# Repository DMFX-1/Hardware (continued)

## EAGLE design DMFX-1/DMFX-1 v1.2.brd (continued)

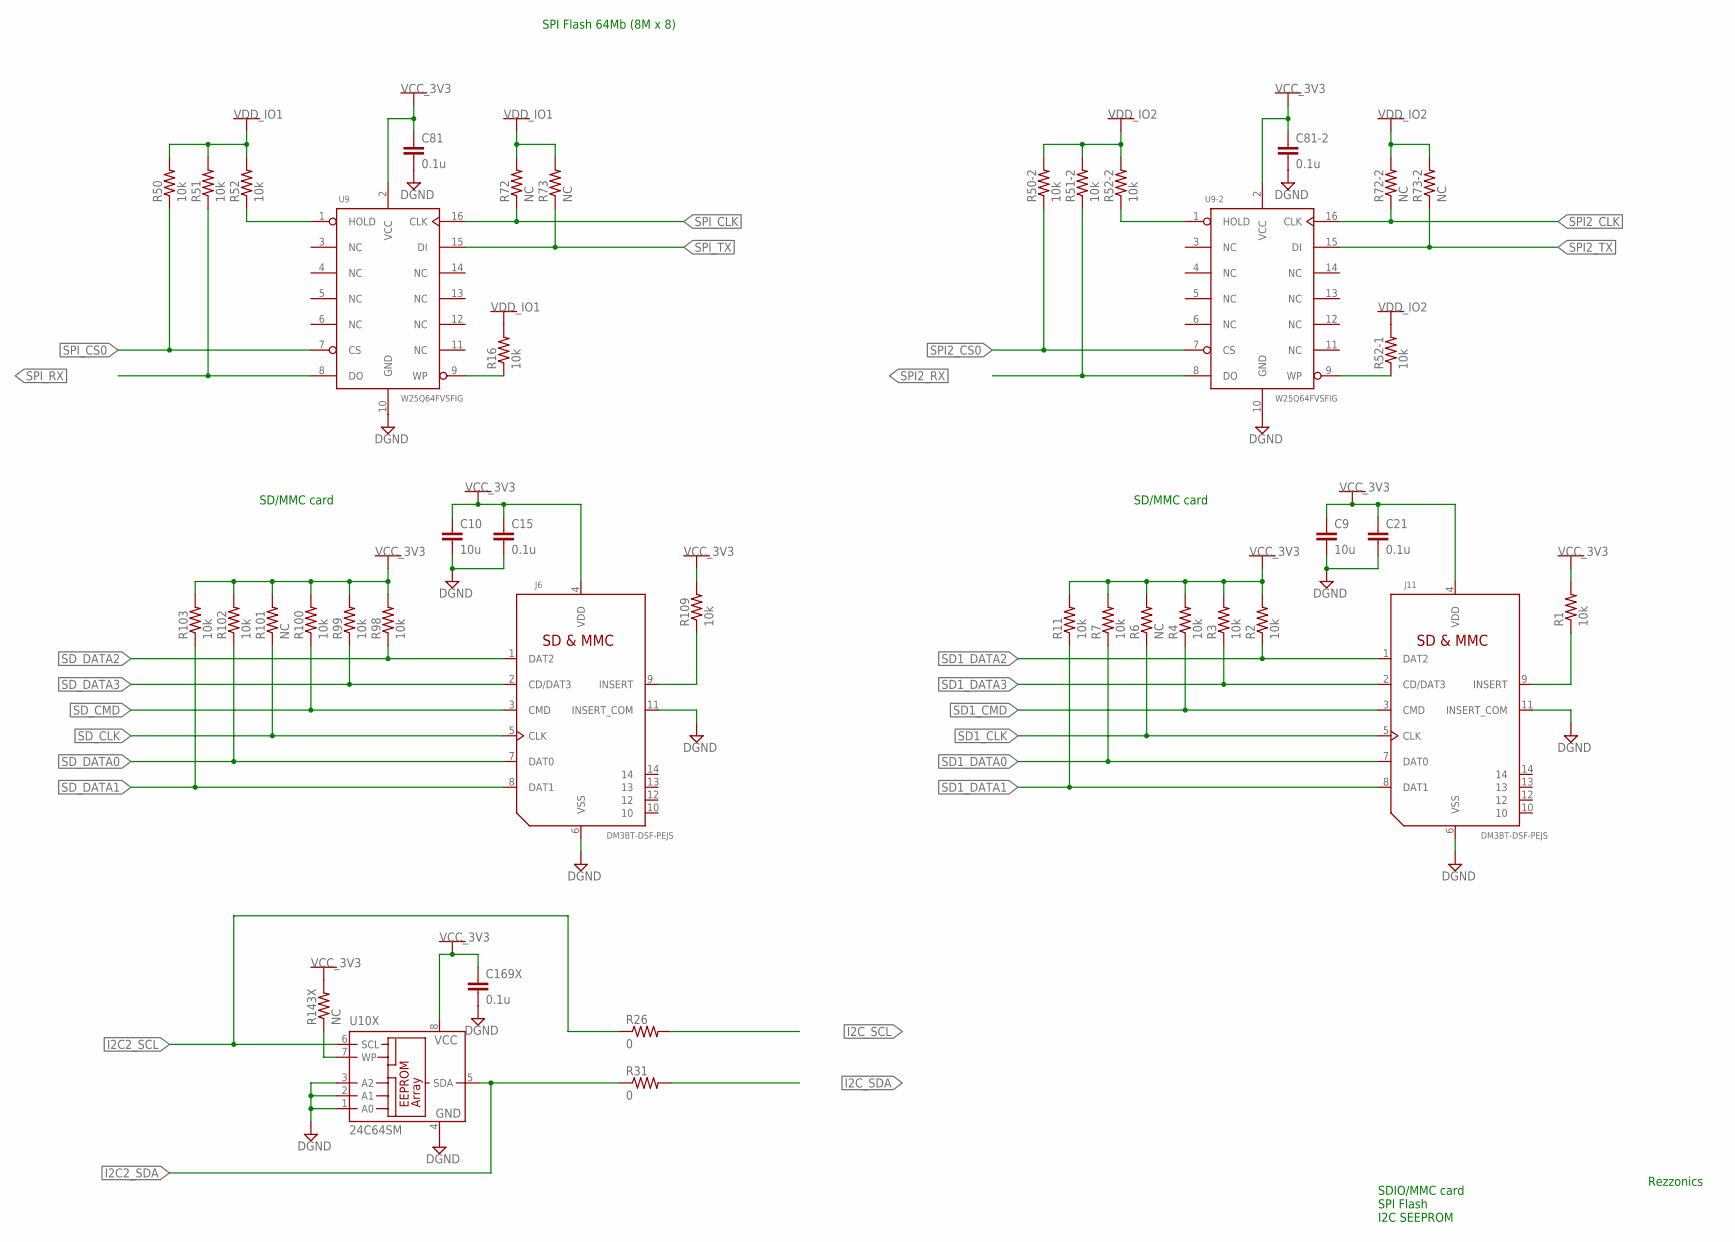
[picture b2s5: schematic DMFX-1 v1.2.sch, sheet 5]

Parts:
C9, C10: 10u; C0603K; MPN GRM188R61C106MA73D
C15, C21, C81, C81-2, C169X: 0.1u; C0402K; MPN GRM155R71C104JA88D
J6, J11: DM3BT-DSF-PEJS; MICROSD_RBT; MPN DM3BT-DSF-PEJS
R1, R2, R3, R4, R7, R11, R16, R50, R50-2, R51, R51-2, R52, R52-1, R52-2, R98, R99, R100, R102, R103, R109: 10k; 0402-RES; MPN ERJ-2RKF1002X
R6, R72, R72-2, R73, R73-2, R101: NC; 0402-RES; MPN *
R26, R31: 0; 0402-RES; MPN ERJ-2GE0R00X
R143X: NC; 0402-RES
U9, U9-2: W25Q64FVSFIG; SO16L; MPN W25Q64FVSFIG
U10X: 24C64SM; SO-08M; MPN AT24C64D-SSHM-T

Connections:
DGND: C9.2, C10.2, C15.2, C21.2, C81.2, C81-2.2, C169X.2, J6.6 (VSS), J6.11 (INSERT_COM), J11.6 (VSS), J11.11 (INSERT_COM), U9.10 (GND), U9-2.10 (GND), U10X.1 (A0), U10X.2 (A1), U10X.3 (A2), U10X.4 (GND); also elsewhere on the board
I2C2_SCL: R26.1, U10X.6 (SCL); also elsewhere on the board
I2C2_SDA: R31.1, U10X.5 (SDA); also elsewhere on the board
I2C_SCL: R26.2; also elsewhere on the board
I2C_SDA: R31.2; also elsewhere on the board
unnamed: J11.9 (INSERT), R1.1
unnamed: R16.1, U9.9 (WP)
unnamed: R52-1.1, U9-2.9 (WP)
unnamed: R52.1, U9.1 (HOLD)
unnamed: J6.9 (INSERT), R109.1
unnamed: R52-2.1, U9-2.1 (HOLD)
unnamed: R143X.1, U10X.7 (WP)
SD1_CLK: J11.5 (CLK), R6.1; also elsewhere on the board
SD1_CMD: J11.3 (CMD), R4.1; also elsewhere on the board
SD1_DATA0: J11.7 (DAT0), R7.1; also elsewhere on the board
SD1_DATA1: J11.8 (DAT1), R11.1; also elsewhere on the board
SD1_DATA2: J11.1 (DAT2), R2.1; also elsewhere on the board
SD1_DATA3: J11.2 (CD/DAT3), R3.1; also elsewhere on the board
SD_CLK: J6.5 (CLK), R101.1; also elsewhere on the board
SD_CMD: J6.3 (CMD), R100.1; also elsewhere on the board
SD_DATA0: J6.7 (DAT0), R102.1; also elsewhere on the board
SD_DATA1: J6.8 (DAT1), R103.1; also elsewhere on the board
SD_DATA2: J6.1 (DAT2), R98.1; also elsewhere on the board
SD_DATA3: J6.2 (CD/DAT3), R99.1; also elsewhere on the board
SPI2_CLK: R72-2.1, U9-2.16 (CLK); also elsewhere on the board
SPI2_CS0: R50-2.1, U9-2.7 (CS); also elsewhere on the board
SPI2_RX: R51-2.1, U9-2.8 (DO); also elsewhere on the board
SPI2_TX: R73-2.1, U9-2.15 (DI); also elsewhere on the board
SPI_CLK: R72.1, U9.16 (CLK); also elsewhere on the board
SPI_CS0: R50.1, U9.7 (CS); also elsewhere on the board
SPI_RX: R51.1, U9.8 (DO); also elsewhere on the board
SPI_TX: R73.1, U9.15 (DI); also elsewhere on the board
VCC_3V3: C9.1, C10.1, C15.1, C21.1, C81.1, C81-2.1, C169X.1, J6.4 (VDD), J11.4 (VDD), R1.2, R2.2, R3.2, R4.2, R6.2, R7.2, R11.2, R98.2, R99.2, R100.2, R101.2, R102.2, R103.2, R109.2, R143X.2, U9.2 (VCC), U9-2.2 (VCC), U10X.8 (VCC); also elsewhere on the board
VDD_IO1: R16.2, R50.2, R51.2, R52.2, R72.2, R73.2; also elsewhere on the board
VDD_IO2: R50-2.2, R51-2.2, R52-1.2, R52-2.2, R72-2.2, R73-2.2; also elsewhere on the board

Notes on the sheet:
SD/MMC card
SPI Flash 64Mb (8M x 8)
Rezzonics
SDIO/MMC card SPI Flash I2C SEEPROM

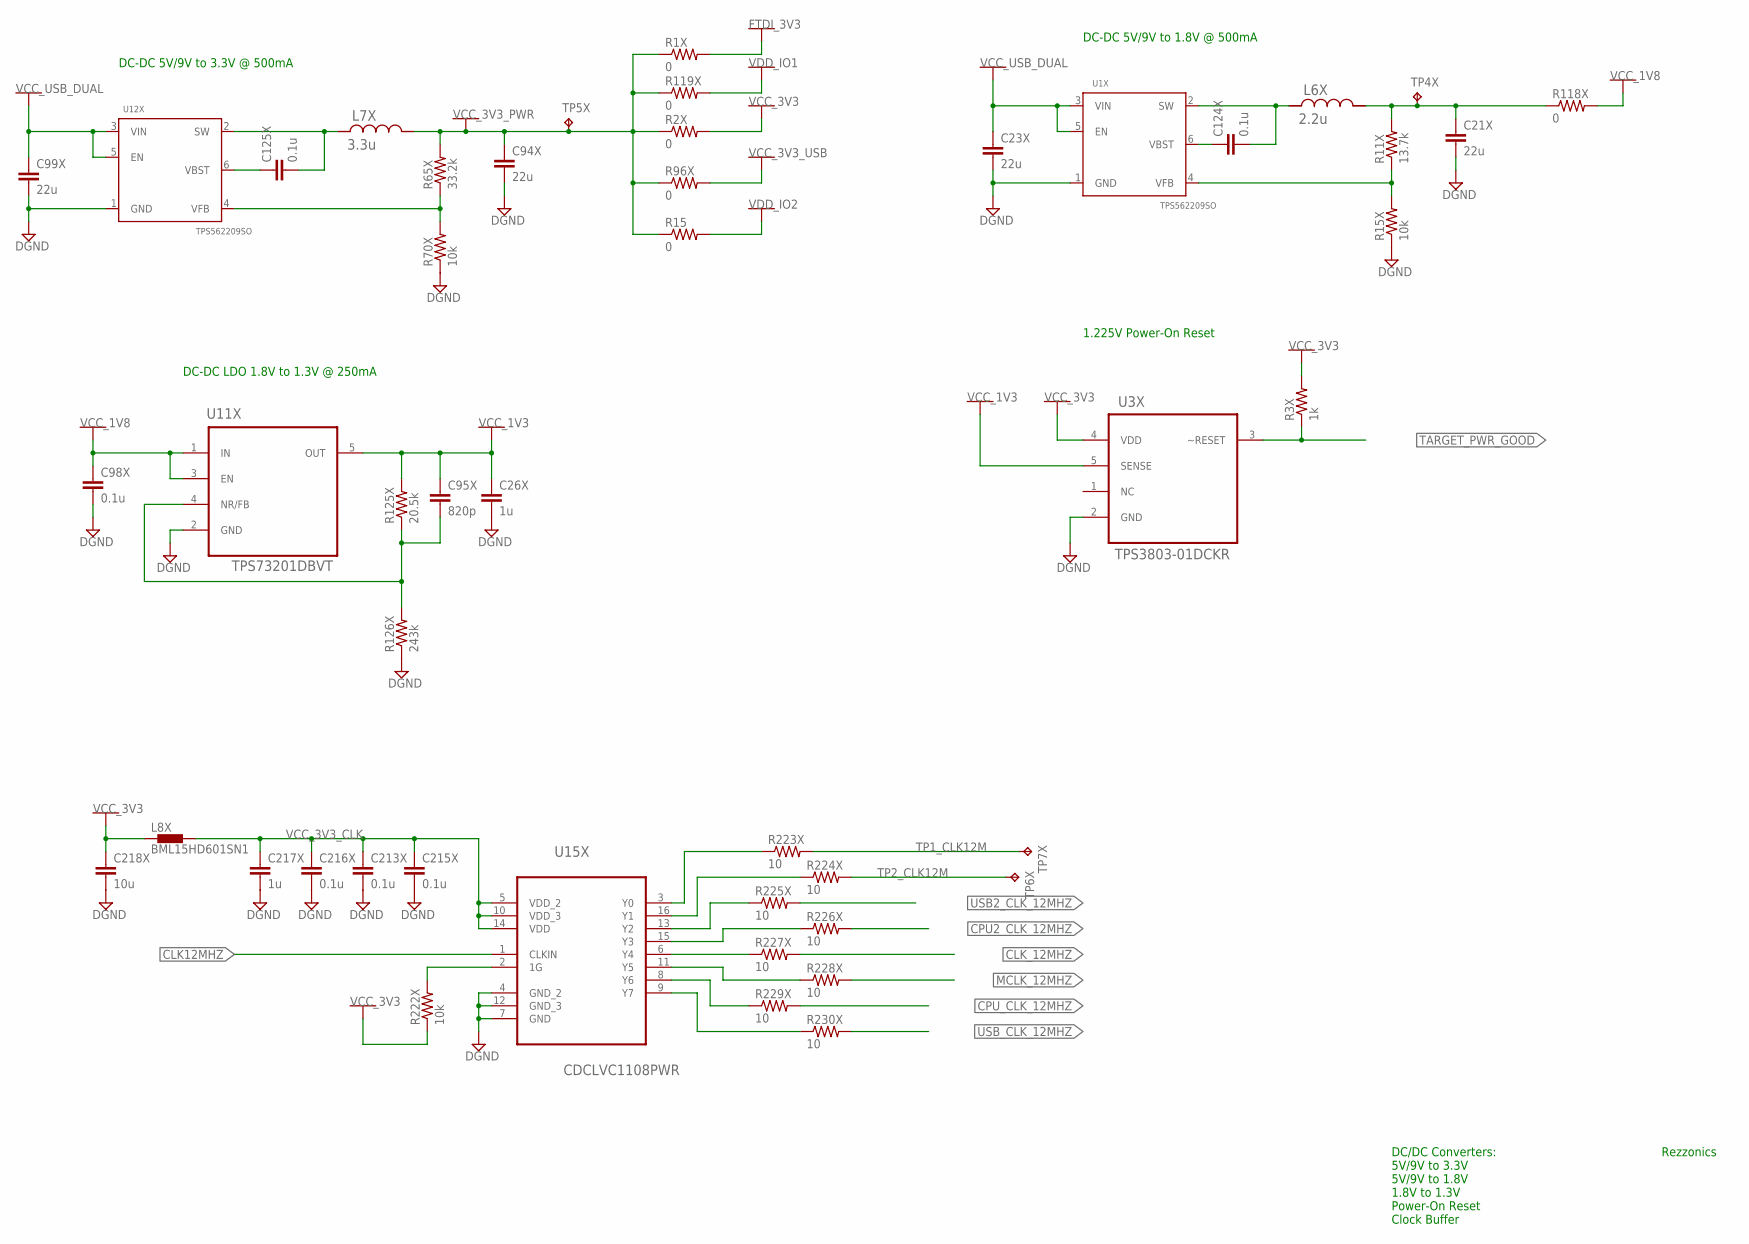
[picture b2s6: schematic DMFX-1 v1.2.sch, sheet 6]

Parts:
C21X, C94X: 22u; C1206K; MPN GRM31CR71A226KE15L
C23X, C99X: 22u; C1210K; MPN GRM32ER71E226ME15L
C26X, C217X: 1u; C0402K; MPN GRM155R70J105KA12D
C95X: 820p; C0402K; MPN GRM1555C1H821JA01D
C98X, C124X, C125X, C213X, C215X, C216X: 0.1u; C0402K; MPN GRM155R71C104JA88D
C218X: 10u; C0603K; MPN GRM188R61C106MA73D
L6X: 2.2u; SRN3015; MPN SRN3015-2R2M
L7X: 3.3u; SRN3015; MPN SRN3015-3R3M
L8X: BML15HD601SN1; 0402; MPN BLM15HD601SN1D
R1X, R2X, R15, R96X, R118X, R119X: 0; 0402-RES; MPN ERJ-2GE0R00X
R3X: 1k; 0402-RES; MPN ERJ-2RKF1001X
R11X: 13.7k; 0402-RES; MPN ERJ-2RKF1372X
R15X, R70X, R222X: 10k; 0402-RES; MPN ERJ-2RKF1002X
R65X: 33.2k; 0402-RES; MPN ERJ-2RKF3322X
R125X: 20.5k; 0402-RES; MPN ERJ-2RKF2052X
R126X: 243k; 0402-RES; MPN ERJ-2RKF2433X
R223X, R224X, R225X, R226X, R227X, R228X, R229X, R230X: 10; 0402-RES; MPN ERJ-2RKF10R0X
TP4X, TP5X, TP6X, TP7X: TPTP06R; TP06R; MPN *
U1X, U12X: TPS562209SO; SOT95P280X145-6N; MPN TPS562209DDCT
U3X: TPS3803-01DCKR; SOT65P210X110-5N; MPN TPS3803-01DCKR
U11X: TPS73201DBVT; SOT95P280X145-5N; MPN TPS73201DBVT
U15X: CDCLVC1108PWR; SOP65P640X120-16N; MPN CDCLVC1108PWR

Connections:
CLK12MHZ: U15X.1 (CLKIN); also elsewhere on the board
CLK_12MHZ: R227X.2; also elsewhere on the board
CPU2_CLK_12MHZ: R226X.2; also elsewhere on the board
CPU_CLK_12MHZ: R229X.2; also elsewhere on the board
DGND: C21X.2, C23X.2, C26X.2, C94X.2, C98X.2, C99X.2, C213X.2, C215X.2, C216X.2, C217X.2, C218X.2, R15X.1, R70X.1, R126X.1, U1X.1 (GND), U3X.2 (GND), U11X.2 (GND), U12X.1 (GND), U15X.4 (GND_2), U15X.7 (GND), U15X.12 (GND_3); also elsewhere on the board
FTDI_3V3: R1X.2; also elsewhere on the board
MCLK_12MHZ: R228X.2; also elsewhere on the board
unnamed: C95X.2, R125X.1, R126X.2, U11X.4 (NR/FB)
unnamed: C125X.1, U12X.6 (VBST)
unnamed: C125X.2, L7X.2, U12X.2 (SW)
unnamed: R65X.1, R70X.2, U12X.4 (VFB)
unnamed: C124X.1, U1X.6 (VBST)
unnamed: C124X.2, L6X.2, U1X.2 (SW)
unnamed: C21X.1, L6X.1, R11X.2, R118X.1, TP4X.TP
unnamed: R11X.1, R15X.2, U1X.4 (VFB)
unnamed: R223X.1, U15X.3 (Y0)
unnamed: R224X.1, U15X.16 (Y1)
unnamed: R225X.1, U15X.13 (Y2)
unnamed: R222X.2, U15X.2 (1G)
unnamed: R226X.1, U15X.15 (Y3)
unnamed: R227X.1, U15X.6 (Y4)
unnamed: R228X.1, U15X.11 (Y5)
unnamed: R229X.1, U15X.8 (Y6)
unnamed: R230X.1, U15X.9 (Y7)
TARGET_PWR_GOOD: R3X.1, U3X.3 (~RESET); also elsewhere on the board
TP1_CLK12M: R223X.2, TP7X.TP
TP2_CLK12M: R224X.2, TP6X.TP
USB2_CLK_12MHZ: R225X.2; also elsewhere on the board
USB_CLK_12MHZ: R230X.2; also elsewhere on the board
VCC_1V3: C26X.1, C95X.1, R125X.2, U3X.5 (SENSE), U11X.5 (OUT); also elsewhere on the board
VCC_1V8: C98X.1, R118X.2, U11X.1 (IN), U11X.3 (EN); also elsewhere on the board
VCC_3V3: C218X.1, L8X.1, R2X.2, R3X.2, R222X.1, U3X.4 (VDD); also elsewhere on the board
VCC_3V3_CLK: C213X.1, C215X.1, C216X.1, C217X.1, L8X.2, U15X.5 (VDD_2), U15X.10 (VDD_3), U15X.14 (VDD)
VCC_3V3_PWR: C94X.1, L7X.1, R1X.1, R2X.1, R15.1, R65X.2, R96X.1, R119X.1, TP5X.TP; also elsewhere on the board
VCC_3V3_USB: R96X.2; also elsewhere on the board
VCC_USB_DUAL: C23X.1, C99X.1, U1X.3 (VIN), U1X.5 (EN), U12X.3 (VIN), U12X.5 (EN); also elsewhere on the board
VDD_IO1: R119X.2; also elsewhere on the board
VDD_IO2: R15.2; also elsewhere on the board

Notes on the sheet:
DC-DC 5V/9V to 3.3V @ 500mA
DC-DC 5V/9V to 1.8V @ 500mA
1.225V Power-On Reset
DC-DC LDO 1.8V to 1.3V @ 250mA
Rezzonics
DC/DC Converters: 5V/9V to 3.3V 5V/9V to 1.8V 1.8V to 1.3V Power-On Reset Clock Buffer

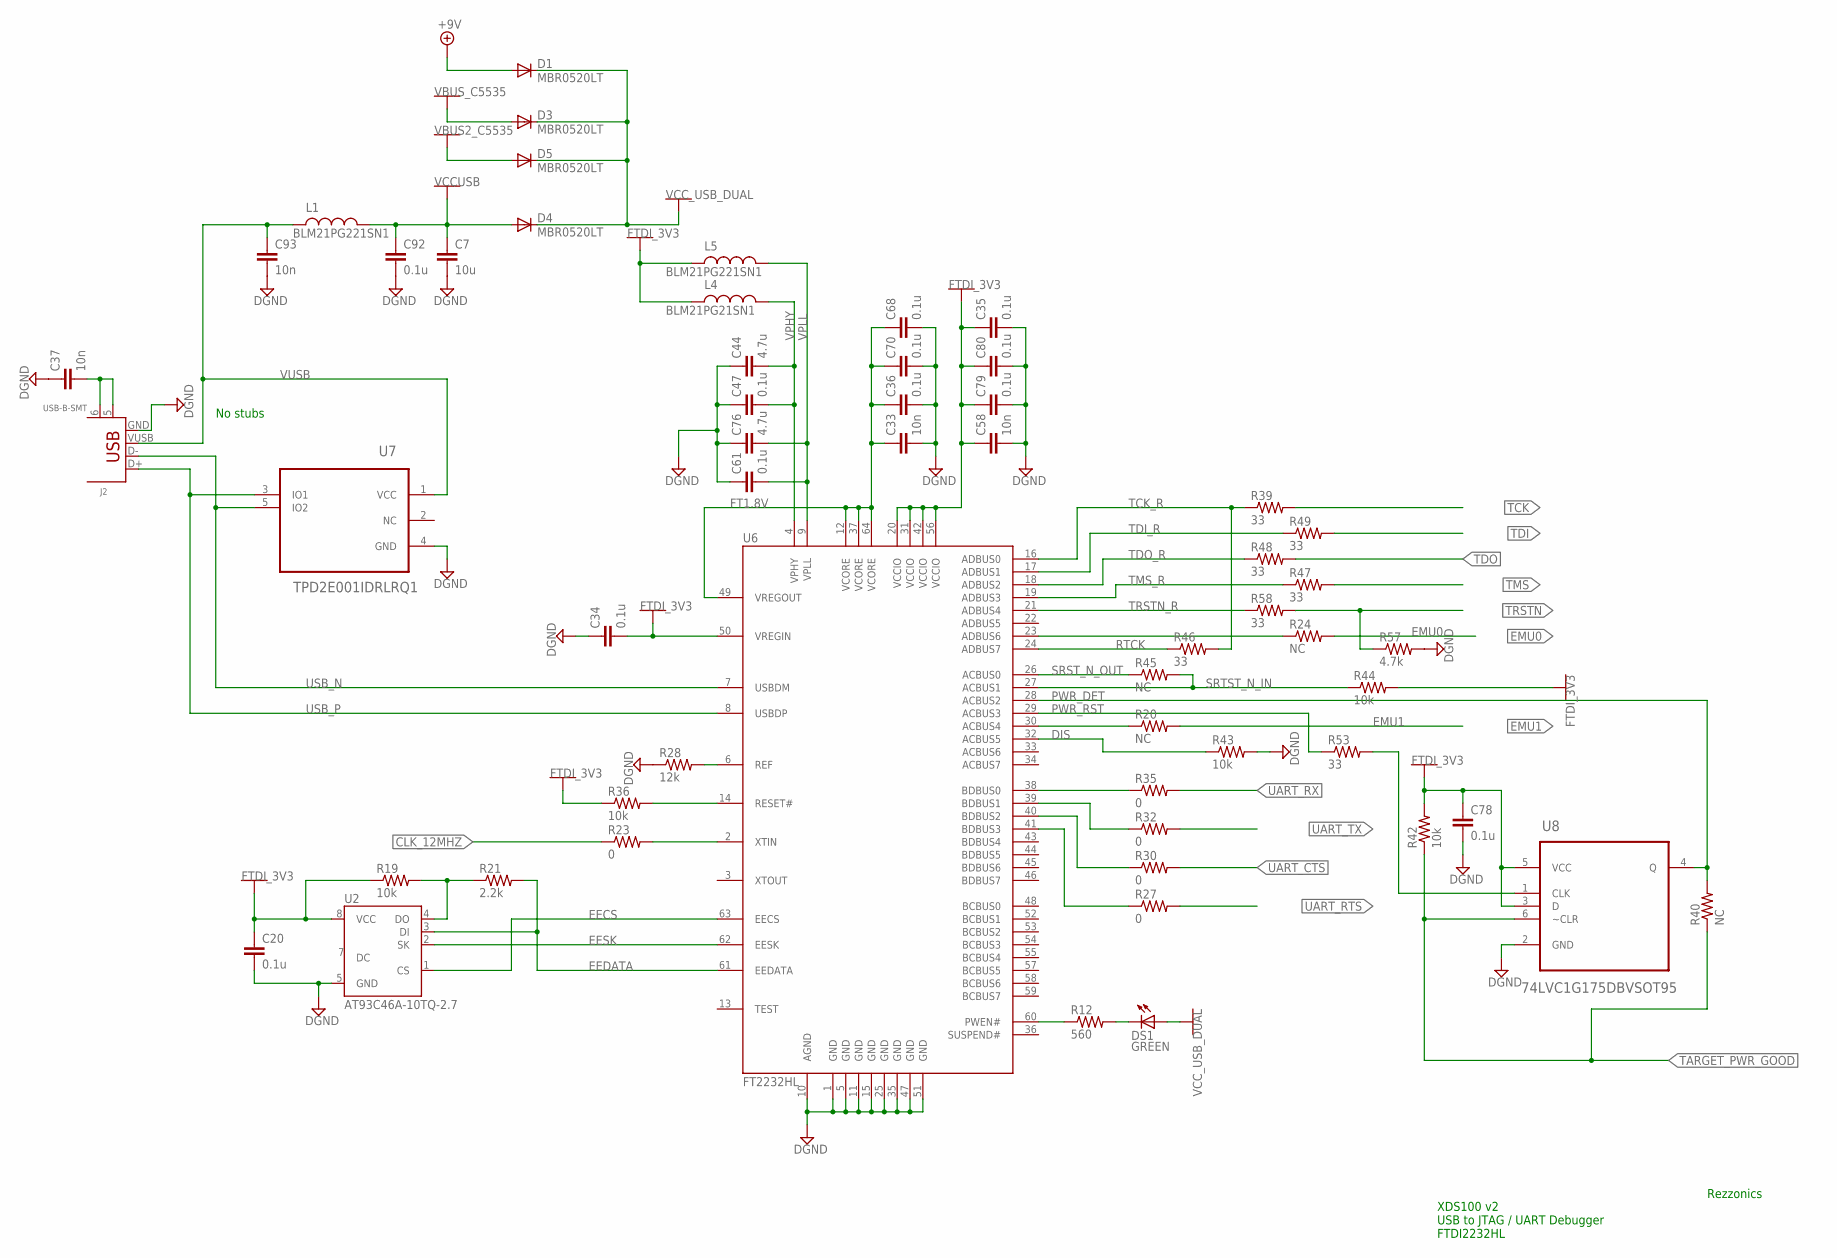
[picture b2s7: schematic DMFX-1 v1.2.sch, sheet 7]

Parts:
C7: 10u; C0603K; MPN GRM188R61C106MA73D
C20, C34, C35, C36, C47, C61, C68, C70, C78, C79, C80, C92: 0.1u; C0402K; MPN GRM155R71C104JA88D
C33, C37, C58, C93: 10n; C0402K; MPN GRM155R71E103KA01D
C44, C76: 4.7u; C0603K; MPN GRM188R60J475KE19D
D1, D3, D4, D5: MBR0520LT; SOD123; MPN MBR0520LT1G
DS1: GREEN; CHIPLED_1206; MPN LTST-C230KGKT
J2: USB-B-SMT; MPN M701-370442
L1, L5: BLM21PG221SN1; 0805; MPN BLM21PG221SN1D
L4: BLM21PG21SN1; 0805; MPN BLM21PG221SN1D
R12: 560; 0402-RES; MPN ERJ-2RKF2200X
R19, R36, R42, R43, R44: 10k; 0402-RES; MPN ERJ-2RKF1002X
R20, R24: NC; 0402-RES
R21: 2.2k; 0402-RES; MPN ERJ-2RKF2201X
R23, R27, R30, R32, R35: 0; 0402-RES; MPN ERJ-2GE0R00X
R28: 12k; 0402-RES; MPN ERJ-2RKF1202X
R39, R46, R47, R48, R49, R53, R58: 33; 0402-RES; MPN ERJ-2RKF33R0X
R40, R45: NC; 0402-RES; MPN *
R57: 4.7k; 0402-RES; MPN ERJ-2RKF4701X
U2: AT93C46A-10TQ-2.7; TSSOP8; MPN AT93C46D-TH-T
U6: FT2232HL; LQFP-10X10-64; MPN FT2232HL-REEL
U7: TPD2E001IDRLRQ1; SOT50P160X60-5N; MPN TPD2E001DRLR
U8: 74LVC1G175DBVSOT95; SOT95P280X145-6N; MPN SN74LVC1G175DBVT

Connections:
CLK_12MHZ: R23.1; also elsewhere on the board
DGND: C7.2, C20.2, C33.2, C34.1, C35.2, C36.2, C37.1, C44.1, C47.1, C58.2, C61.1, C68.2, C70.2, C76.1, C78.2, C79.2, C80.2, C92.2, C93.2, J2.GND, R28.1, R43.2, R57.2, U2.5 (GND), U6.1 (GND), U6.5 (GND), U6.10 (AGND), U6.11 (GND), U6.15 (GND), U6.25 (GND), U6.35 (GND), U6.47 (GND), U6.51 (GND), U7.4 (GND), U8.2 (GND); also elsewhere on the board
DIS: R43.1, U6.32 (ACBUS5)
EECS: U2.1 (CS), U6.63 (EECS)
EEDATA: R21.2, U2.3 (DI), U6.61 (EEDATA)
EESK: U2.2 (SK), U6.62 (EESK)
EMU0: R24.2; also elsewhere on the board
EMU1: R20.2; also elsewhere on the board
FT1.8V: C33.1, C36.1, C68.1, C70.1, U6.12 (VCORE), U6.37 (VCORE), U6.49 (VREGOUT), U6.64 (VCORE)
FTDI_3V3: C20.1, C34.2, C35.1, C58.1, C78.1, C79.1, C80.1, L4.1, L5.1, R19.1, R36.1, R42.2, R44.2, U2.8 (VCC), U6.20 (VCCIO), U6.31 (VCCIO), U6.42 (VCCIO), U6.50 (VREGIN), U6.56 (VCCIO), U8.3 (D), U8.5 (VCC); also elsewhere on the board
unnamed: R20.1, U6.30 (ACBUS4)
unnamed: R24.1, U6.23 (ADBUS6)
unnamed: R36.2, U6.14 (RESET#)
unnamed: R23.2, U6.2 (XTIN)
unnamed: R28.2, U6.6 (REF)
unnamed: R19.2, R21.1, U2.4 (DO)
unnamed: DS1.C, R12.2
unnamed: R12.1, U6.60 (PWEN#)
unnamed: C37.2, J2.5, J2.6
unnamed: R53.2, U8.1 (CLK)
unnamed: R35.1, U6.38 (BDBUS0)
unnamed: R32.1, U6.39 (BDBUS1)
unnamed: R30.1, U6.40 (BDBUS2)
unnamed: R27.1, U6.41 (BDBUS3)
PWR_DET: R40.2, U6.28 (ACBUS2), U8.4 (Q)
PWR_RST: R53.1, U6.29 (ACBUS3)
RTCK: R46.1, U6.24 (ADBUS7)
SRST_N_OUT: R45.1, U6.26 (ACBUS0)
SRTST_N_IN: R44.1, R45.2, U6.27 (ACBUS1)
TARGET_PWR_GOOD: R40.1, R42.1, U8.6 (~CLR); also elsewhere on the board
TCK: R39.2; also elsewhere on the board
TCK_R: R39.1, R46.2, U6.16 (ADBUS0)
TDI: R49.2; also elsewhere on the board
TDI_R: R49.1, U6.17 (ADBUS1)
TDO: R48.2; also elsewhere on the board
TDO_R: R48.1, U6.18 (ADBUS2)
TMS: R47.2; also elsewhere on the board
TMS_R: R47.1, U6.19 (ADBUS3)
TRSTN: R57.1, R58.2; also elsewhere on the board
TRSTN_R: R58.1, U6.21 (ADBUS4)
UART_CTS: R30.2; also elsewhere on the board
UART_RTS: R27.2; also elsewhere on the board
UART_RX: R35.2; also elsewhere on the board
UART_TX: R32.2; also elsewhere on the board
USB_N: J2.D-, U6.7 (USBDM), U7.5 (IO2)
USB_P: J2.D+, U6.8 (USBDP), U7.3 (IO1)
V3.3AA: D1.A; also elsewhere on the board
VBUS2_C5535: D5.A; also elsewhere on the board
VBUS_C5535: D3.A; also elsewhere on the board
VCCUSB: C7.1, C92.1, D4.A, L1.2
VCC_USB_DUAL: D1.C, D3.C, D4.C, D5.C, DS1.A; also elsewhere on the board
VPHY: C44.2, C47.2, L4.2, U6.4 (VPHY)
VPLL: C61.2, C76.2, L5.2, U6.9 (VPLL)
VUSB: C93.1, J2.VUSB (VBUS), L1.1, U7.1 (VCC)

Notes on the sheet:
No stubs
Rezzonics
XDS100 v2 USB to JTAG / UART Debugger FTDI2232HL

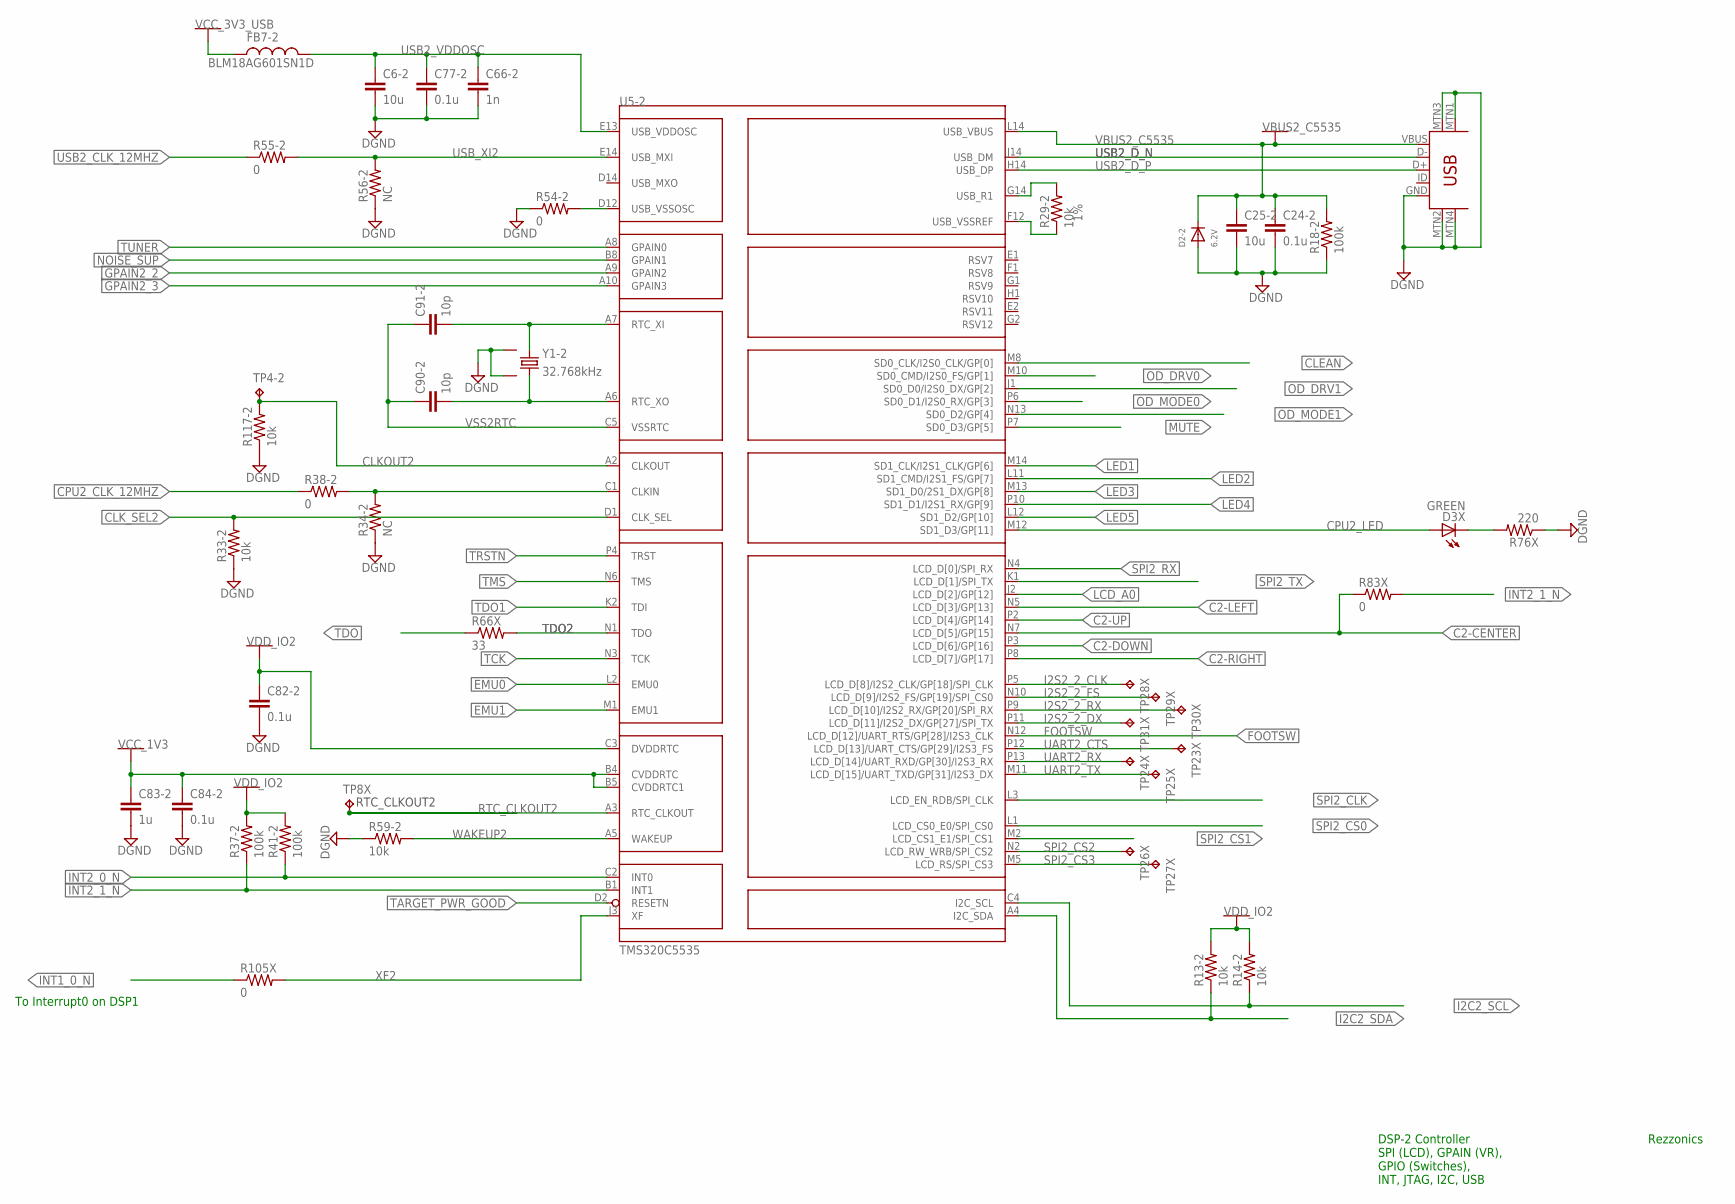
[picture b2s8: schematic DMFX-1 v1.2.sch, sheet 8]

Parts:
C6-2, C25-2: 10u; C0603K; MPN GRM188R61C106MA73D
C24-2, C77-2: 0.1u; C0402K; MPN GRM155R71C104JA88D
C66-2: 1n; 0402; MPN GRM155R71H102JA01J
C82-2, C84-2: 0.1u; 0402; MPN GRM155R71C104JA88D
C83-2: 1u; 0402; MPN GRM155R70J105KA12D
C90-2, C91-2: 10p; C0402K; MPN GRM1555C1H100FA01D
D2-2: 6.2V; SMADIODE; MPN 1SMA5920BT3G
D3X: GREEN; CHIPLED_0603; MPN LTST-C190KGKT
FB7-2: BLM18AG601SN1D; 0805; MPN BLM21AG151SN1D
J1-2: USB-MINIB-5PIN; USB-MINIB; MPN 10033526-N3212LF
R13-2, R14-2, R33-2, R59-2, R117-2: 10k; 0402-RES; MPN ERJ-2RKF1002X
R18-2, R37-2, R41-2: 100k; 0402-RES; MPN ERJ-2RKF1003X
R29-2: 10k; 0402; TOLERANCE 1%; MPN ERJ-2RKF1002X
R34-2: NC; 0402; MPN *
R38-2, R54-2, R83X: 0; 0402; MPN ERJ-2GE0R00X
R55-2, R105X: 0; 0402-RES; MPN ERJ-2GE0R00X
R56-2: NC; 0402-RES; MPN *
R66X: 33; 0402-RES; MPN ERJ-2RKF33R0X
R76X: 220; 0402-RES; MPN ERJ-2RKF2200X
TP4-2, TP8X, TP23X, TP24X, TP25X, TP26X, TP27X, TP28X, TP29X, TP30X, TP31X: TPTP06R; TP06R; MPN *
U5: TMS320C5535; PBGA144; MPN TMS320C5535AZHH10
Y1-2: 32.768kHz; CRYSTAL-32KHZ-SMD_EPSON_MC146; MPN SSPT7F-12.5PF20-R

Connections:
C2-CENTER: R83X.1, U5.N7 (LCD_D[5]/GP[15]); also elsewhere on the board
C2-DOWN: U5.P3 (LCD_D[6]/GP[16]); also elsewhere on the board
C2-LEFT: U5.N5 (LCD_D[3]/GP[13]); also elsewhere on the board
C2-RIGHT: U5.P8 (LCD_D[7]/GP[17]); also elsewhere on the board
C2-UP: U5.P2 (LCD_D[4]/GP[14]); also elsewhere on the board
CLEAN: U5.M8 (SD0_CLK/I2S0_CLK/GP[0]); also elsewhere on the board
CLKOUT2: R117-2.2, TP4-2.TP, U5.A2 (CLKOUT)
CLK_SEL2: R33-2.2, U5.D1 (CLK_SEL)
CPU2_CLK_12MHZ: R38-2.1; also elsewhere on the board
CPU2_LED: D3X.A, U5.M12 (SD1_D3/GP[11])
DGND: C6-2.2, C24-2.2, C25-2.2, C66-2.2, C77-2.2, C82-2.2, C83-2.2, C84-2.2, D2-2.A, J1-2.GND, J1-2.MTN1 (MTN2), J1-2.MTN2 (MTN3), J1-2.MTN3 (MTN1), J1-2.MTN4, R18-2.1, R33-2.1, R34-2.1, R54-2.1, R56-2.1, R59-2.1, R76X.1, R117-2.1, Y1-2.NC1 (3), Y1-2.NC2 (4); also elsewhere on the board
EMU0: U5.L2 (EMU0); also elsewhere on the board
EMU1: U5.M1 (EMU1); also elsewhere on the board
FOOTSW: U5.N12 (LCD_D[12]/UART_RTS/GP[28]/I2S3_CLK); also elsewhere on the board
GPAIN2_2: U5.A9 (GPAIN2); also elsewhere on the board
GPAIN2_3: U5.A10 (GPAIN3); also elsewhere on the board
I2C2_SCL: R14-2.1, U5.C4 (I2C_SCL); also elsewhere on the board
I2C2_SDA: R13-2.1, U5.A4 (I2C_SDA); also elsewhere on the board
I2S2_2_CLK: TP28X.TP, U5.P5 (LCD_D[8]/I2S2_CLK/GP[18]/SPI_CLK)
I2S2_2_DX: TP31X.TP, U5.P11 (LCD_D[11]/I2S2_DX/GP[27]/SPI_TX)
I2S2_2_FS: TP29X.TP, U5.N10 (LCD_D[9]/I2S2_FS/GP[19]/SPI_CS0)
I2S2_2_RX: TP30X.TP, U5.P9 (LCD_D[10]/I2S2_RX/GP[20]/SPI_RX)
INT1_0_N: R105X.1; also elsewhere on the board
INT2_0_N: R41-2.1, U5.C2 (INT0); also elsewhere on the board
INT2_1_N: R37-2.1, R83X.2, U5.B1 (INT1)
LCD_A0: U5.J2 (LCD_D[2]/GP[12]); also elsewhere on the board
LED1: U5.M14 (SD1_CLK/I2S1_CLK/GP[6]); also elsewhere on the board
LED2: U5.L11 (SD1_CMD/I2S1_FS/GP[7]); also elsewhere on the board
LED3: U5.M13 (SD1_D0/2S1_DX/GP[8]); also elsewhere on the board
LED4: U5.P10 (SD1_D1/I2S1_RX/GP[9]); also elsewhere on the board
LED5: U5.L12 (SD1_D2/GP[10]); also elsewhere on the board
MUTE: U5.P7 (SD0_D3/GP[5]); also elsewhere on the board
unnamed: C91-2.2, U5.A7 (RTC_XI), Y1-2.P$2 (2)
unnamed: C90-2.2, U5.A6 (RTC_XO), Y1-2.P$1 (1)
unnamed: R34-2.2, R38-2.2, U5.C1 (CLKIN)
unnamed: D3X.C, R76X.2
unnamed: R29-2.2, U5.G14 (USB_R1)
NOISE_SUP: U5.B8 (GPAIN1); also elsewhere on the board
OD_DRV0: U5.M10 (SD0_CMD/I2S0_FS/GP[1]); also elsewhere on the board
OD_DRV1: U5.J1 (SD0_D0/I2S0_DX/GP[2]); also elsewhere on the board
OD_MODE0: U5.P6 (SD0_D1/I2S0_RX/GP[3]); also elsewhere on the board
OD_MODE1: U5.N13 (SD0_D2/GP[4]); also elsewhere on the board
RTC_CLKOUT2: TP8X.TP, U5.A3 (RTC_CLKOUT)
SPI2_CLK: U5.L3 (LCD_EN_RDB/SPI_CLK); also elsewhere on the board
SPI2_CS0: U5.L1 (LCD_CS0_E0/SPI_CS0); also elsewhere on the board
SPI2_CS1: U5.M2 (LCD_CS1_E1/SPI_CS1); also elsewhere on the board
SPI2_CS2: TP26X.TP, U5.N2 (LCD_RW_WRB/SPI_CS2)
SPI2_CS3: TP27X.TP, U5.M5 (LCD_RS/SPI_CS3)
SPI2_RX: U5.N4 (LCD_D[0]/SPI_RX); also elsewhere on the board
SPI2_TX: U5.K1 (LCD_D[1]/SPI_TX); also elsewhere on the board
TARGET_PWR_GOOD: U5.D2 (RESETN); also elsewhere on the board
TCK: U5.N3 (TCK); also elsewhere on the board
TDO: R66X.1; also elsewhere on the board
TDO1: U5.K2 (TDI); also elsewhere on the board
TDO2: R66X.2, U5.N1 (TDO)
TMS: U5.N6 (TMS); also elsewhere on the board
TRSTN: U5.P4 (TRST); also elsewhere on the board
TUNER: U5.A8 (GPAIN0); also elsewhere on the board
UART2_CTS: TP23X.TP, U5.P12 (LCD_D[13]/UART_CTS/GP[29]/I2S3_FS)
UART2_RX: TP24X.TP, U5.P13 (LCD_D[14]/UART_RXD/GP[30]/I2S3_RX)
UART2_TX: TP25X.TP, U5.M11 (LCD_D[15]/UART_TXD/GP[31]/I2S3_DX)
USB2_CLK_12MHZ: R55-2.1; also elsewhere on the board
USB2_D_N: J1-2.D-, U5.J14 (USB_DM)
USB2_D_P: J1-2.D+, U5.H14 (USB_DP)
USB2_VDDOSC: C6-2.1, C66-2.1, C77-2.1, FB7-2.2, U5.E13 (USB_VDDOSC)
USB2_VSSOSC: R54-2.2, U5.D12 (USB_VSSOSC)
USB2_VSSREF: R29-2.1, U5.F12 (USB_VSSREF)
USB_XI2: R55-2.2, R56-2.2, U5.E14 (USB_MXI)
VBUS2_C5535: C24-2.1, C25-2.1, D2-2.C, J1-2.VBUS, R18-2.2, U5.L14 (USB_VBUS); also elsewhere on the board
VCC_1V3: C83-2.1, C84-2.1, U5.B4 (CVDDRTC), U5.B5 (CVDDRTC1); also elsewhere on the board
VCC_3V3_USB: FB7-2.1; also elsewhere on the board
VDD_IO2: C82-2.1, R13-2.2, R14-2.2, R37-2.2, R41-2.2, U5.C3 (DVDDRTC); also elsewhere on the board
VSS2RTC: C90-2.1, C91-2.1, U5.C5 (VSSRTC)
WAKEUP2: R59-2.2, U5.A5 (WAKEUP)
XF2: R105X.2, U5.J3 (XF)

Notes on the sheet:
To Interrupt0 on DSP1
Rezzonics
DSP-2 Controller SPI (LCD), GPAIN (VR), GPIO (Switches), INT, JTAG, I2C, USB

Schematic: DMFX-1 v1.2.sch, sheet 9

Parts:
C1-2, C3-2, C4-2: 10u; C0603K; MPN GRM188R61C106MA73D
C2-2, C5-2: 1u; C0402K; MPN GRM155R70J105KA12D
C28-2, C29-2, C30-2, C32-2, C40-2, C45-2, C46-2, C48-2, C49-2, C57-2, C59-2, C60-2, C62-2, C63-2, C65-2, C67-2, C69-2, C71-2, C72-2, C75-2, C85-2, C87-2, C88-2: 0.1u; 0402; MPN GRM155R71C104JA88D
C38-2, C41-2, C43-2, C51-2, C55-2, C73-2: 10n; 0402; MPN GRM155R71E103KA01D
C42-2, C52-2, C53-2, C54-2, C64-2, C86-2: 1u; 0402; MPN GRM155R70J105KA12D
C50-2, C56-2: 1n; 0402; MPN GRM155R71H102JA01J
C74-2: 1n; C0402K; MPN GRM155R71H102JA01J
C89-2: 10n; C0402K; MPN GRM155R71E103KA01D
FB1-2, FB4-2, FB5-2, FB6-2: BLM18AG601SN1D; 0603; MPN BLM18AG601SN1D
L3-2: BLM18AG601SN1D; 0603; MPN BLM18AG601SN1D
R60-2, R61-2, R64-2: 0; 0402-RES; MPN ERJ-2GE0R00X
R62-2, R63-2: NC; 0402-RES; MPN *
R97-2, R122-2, R124-2: 0; 0805; MPN ERJ-6GEY0R00V
R121-2: NC; 0805; MPN *
U5: TMS320C5535; PBGA144; MPN TMS320C5535AZHH10

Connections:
AGND: C2-2.2, C3-2.2, C43-2.2, C49-2.2, C50-2.2, C57-2.2, C73-2.2, C85-2.2, C86-2.2, C88-2.2, FB1-2.2, U5.A1 (VSSA_PLL), U5.B6 (VSSA_ANA), U5.C9 (VSSA_ANA), U5.F13 (USB_VSSPLL), U5.J12 (USB_VSSA1P3); also elsewhere on the board
ANA_LDO_OUT2: C73-2.1, C85-2.1, C86-2.1, U5.B7 (VDDA_ANA), U5.B9 (ANA_LDOO), U5.C7 (VDDA_PLL); also elsewhere on the board
DGND: C1-2.2, C4-2.2, C5-2.2, C28-2.2, C29-2.2, C30-2.2, C32-2.2, C38-2.2, C40-2.2, C41-2.2, C42-2.2, C45-2.2, C46-2.2, C48-2.2, C51-2.2, C52-2.2, C53-2.2, C54-2.2, C55-2.2, C56-2.2, C59-2.2, C60-2.2, C62-2.2, C63-2.2, C64-2.2, C65-2.2, C67-2.2, C69-2.2, C71-2.2, C72-2.2, C74-2.2, C75-2.2, C87-2.2, C89-2.2, FB1-2.1, R60-2.1, R61-2.1, R62-2.1, R64-2.1, U5.A11 (RSV4), U5.A14 (VSS), U5.B2 (VSS), U5.B3 (VSS), U5.B11 (RSV5), U5.C8 (VSS), U5.C12 (VSS), U5.D4 (VSS), U5.D5 (VSS), U5.D10 (VSS), U5.E3 (VSS), U5.E4 (VSS), U5.E11 (VSS), U5.F3 (VSS), U5.H3 (VSS), U5.H13 (USB_VSSA3P3), U5.J13 (VSS), U5.K3 (VSS), U5.K4 (VSS), U5.K14 (USB_VSS1P3), U5.L5 (VSS), U5.L10 (VSS), U5.M7 (VSS), U5.P1 (VSS), U5.P14 (VSS); also elsewhere on the board
DSP2_LDO_OUT: C38-2.1, C40-2.1, C41-2.1, C42-2.1, C46-2.1, C48-2.1, C51-2.1, C52-2.1, C53-2.1, C54-2.1, C55-2.1, C59-2.1, C62-2.1, C64-2.1, C65-2.1, C67-2.1, C69-2.1, C89-2.1, R124-2.2, U5.C11 (CVDD), U5.D3 (CVDD), U5.D11 (CVDD), U5.F2 (CVDD), U5.G3 (CVDD), U5.H2 (CVDD), U5.K11 (CVDD), U5.K12 (RSV1), U5.L13 (RSV2), U5.M6 (CVDD), U5.M9 (CVDD), U5.N9 (CVDD)
DSP2_LDO_OUT_REG: R124-2.1, U5.A13 (DSP_LDOO)
unnamed: R61-2.2, U5.A12 (RSV0)
unnamed: R60-2.2, U5.B12 (RSV3)
unnamed: R62-2.2, U5.B13 (RSV6)
unnamed: C88-2.1, U5.C10 (BG_CAP)
unnamed: R63-2.1, R64-2.2, U5.C13 (DSP_LDO_EN)
USB2_LDO: R122-2.2, U5.D13 (USB_LDOO)
USB2_VDD1P3: C5-2.1, C60-2.1, C74-2.1, FB6-2.2, U5.E12 (USB_VDD1P3), U5.F14 (USB_VDD1P3), U5.K13 (USB_VDD1P3)
USB2_VDDA1P3: C2-2.1, C43-2.1, C49-2.1, FB4-2.2, U5.H12 (USB_VDDA1P3)
USB2_VDDA3P3: C4-2.1, C56-2.1, C63-2.1, FB5-2.2, U5.G12 (USB_VDDA3P3)
USB2_VDDPLL: C3-2.1, C50-2.1, C57-2.1, L3-2.2, U5.G13 (USB_VDDPLL)
USB_LDO_OUT2: FB4-2.1, FB6-2.1, R121-2.2, R122-2.1
VCC_1V3: R121-2.1; also elsewhere on the board
VCC_1V8: C71-2.1, C75-2.1, C87-2.1, R63-2.2, U5.B10 (LDOI), U5.B14 (LDOI), U5.C14 (LDOI); also elsewhere on the board
VCC_3V3_PWR: R97-2.2; also elsewhere on the board
VCC_3V3_USB: FB5-2.1, L3-2.1; also elsewhere on the board
VDD_IO2_CPU: C1-2.1, C28-2.1, C29-2.1, C30-2.1, C32-2.1, C45-2.1, C72-2.1, R97-2.1, U5.C6 (DVDDIO), U5.L4 (DVDDIO), U5.M3 (DVDDIO), U5.M4 (DVDDIO), U5.N8 (DVDDIO), U5.N11 (DVDDIO), U5.N14 (DVDDIO)

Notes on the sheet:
DSP-2 POWER
Rezzonics

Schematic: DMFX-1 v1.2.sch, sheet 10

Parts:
C168X: 100p; C0402K; MPN GRM1555C1H101FA01J
H1, H2, H3, H4: MOUNT-PAD-ROUND3.0; 3,0-PAD; MPN *
J5, J7: 87409-110LF; MPN 87409-110LF
JP2: FOOTSW; 1X02; MPN *
JP3, JP6, JP7, JP8: FIDUCIAL1X2.5; FIDUCIAL-1X2.5; MPN *
LSP1, LSP2: LSP13; MPN *
R4X: 10k; 0402-RES; MPN ERJ-2RKF1002X
SW1: MB2011SB1W03-DA; MB2011; MPN MB2011SB1W03-DA
TP3, TP5, TP6, TP7, TP10: TPTP12R; TP12R; MPN *

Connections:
A-CENTER: J5.10, TP5.TP
A-DOWN: J5.6, TP3.TP
A-LEFT: J5.18, TP7.TP
A-RIGHT: J5.2, TP10.TP
A-UP: J5.14, TP6.TP
ANA_LDO_OUT2: J7.14; also elsewhere on the board
C2-CENTER: J5.12; also elsewhere on the board
C2-DOWN: J5.8; also elsewhere on the board
C2-LEFT: J5.20; also elsewhere on the board
C2-RIGHT: J5.4; also elsewhere on the board
C2-UP: J5.16; also elsewhere on the board
DGND: C168X.2, H1.B3,0, H2.B3,0, H3.B3,0, H4.B3,0, J5.3, J5.7, J5.19, J7.16, J7.18, J7.19, J7.20, JP2.1, LSP1.MP, LSP2.MP, SW1.3 (S); also elsewhere on the board
DISTOCT: J7.10; also elsewhere on the board
DIST_OUT: J7.8; also elsewhere on the board
FOOTSW: C168X.1, SW1.2; also elsewhere on the board
GPAIN0: J7.17; also elsewhere on the board
GPAIN1: J7.15; also elsewhere on the board
GPAIN2: J7.9; also elsewhere on the board
GPAIN2_2: J7.7; also elsewhere on the board
GPAIN2_3: J7.11; also elsewhere on the board
GPAIN3: J7.13; also elsewhere on the board
LCD_A0: J5.13; also elsewhere on the board
LED1: J7.1; also elsewhere on the board
LED2: J7.3; also elsewhere on the board
LED3: J7.4; also elsewhere on the board
LED4: J7.5; also elsewhere on the board
LED5: J7.6; also elsewhere on the board
OCT_OUT: J7.12; also elsewhere on the board
SPI2_CLK: J5.11; also elsewhere on the board
SPI2_CS1: J5.17; also elsewhere on the board
SPI2_TX: J5.9; also elsewhere on the board
SW_UP: JP2.2, R4X.1, SW1.1 (O)
TARGET_PWR_GOOD: J5.15; also elsewhere on the board
VCC_3V3: J5.1, J5.5, J7.2, R4X.2; also elsewhere on the board

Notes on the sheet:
Rezzonics
LCD, Switches, VR Potentiometers
Fiducials
Foot Switch
